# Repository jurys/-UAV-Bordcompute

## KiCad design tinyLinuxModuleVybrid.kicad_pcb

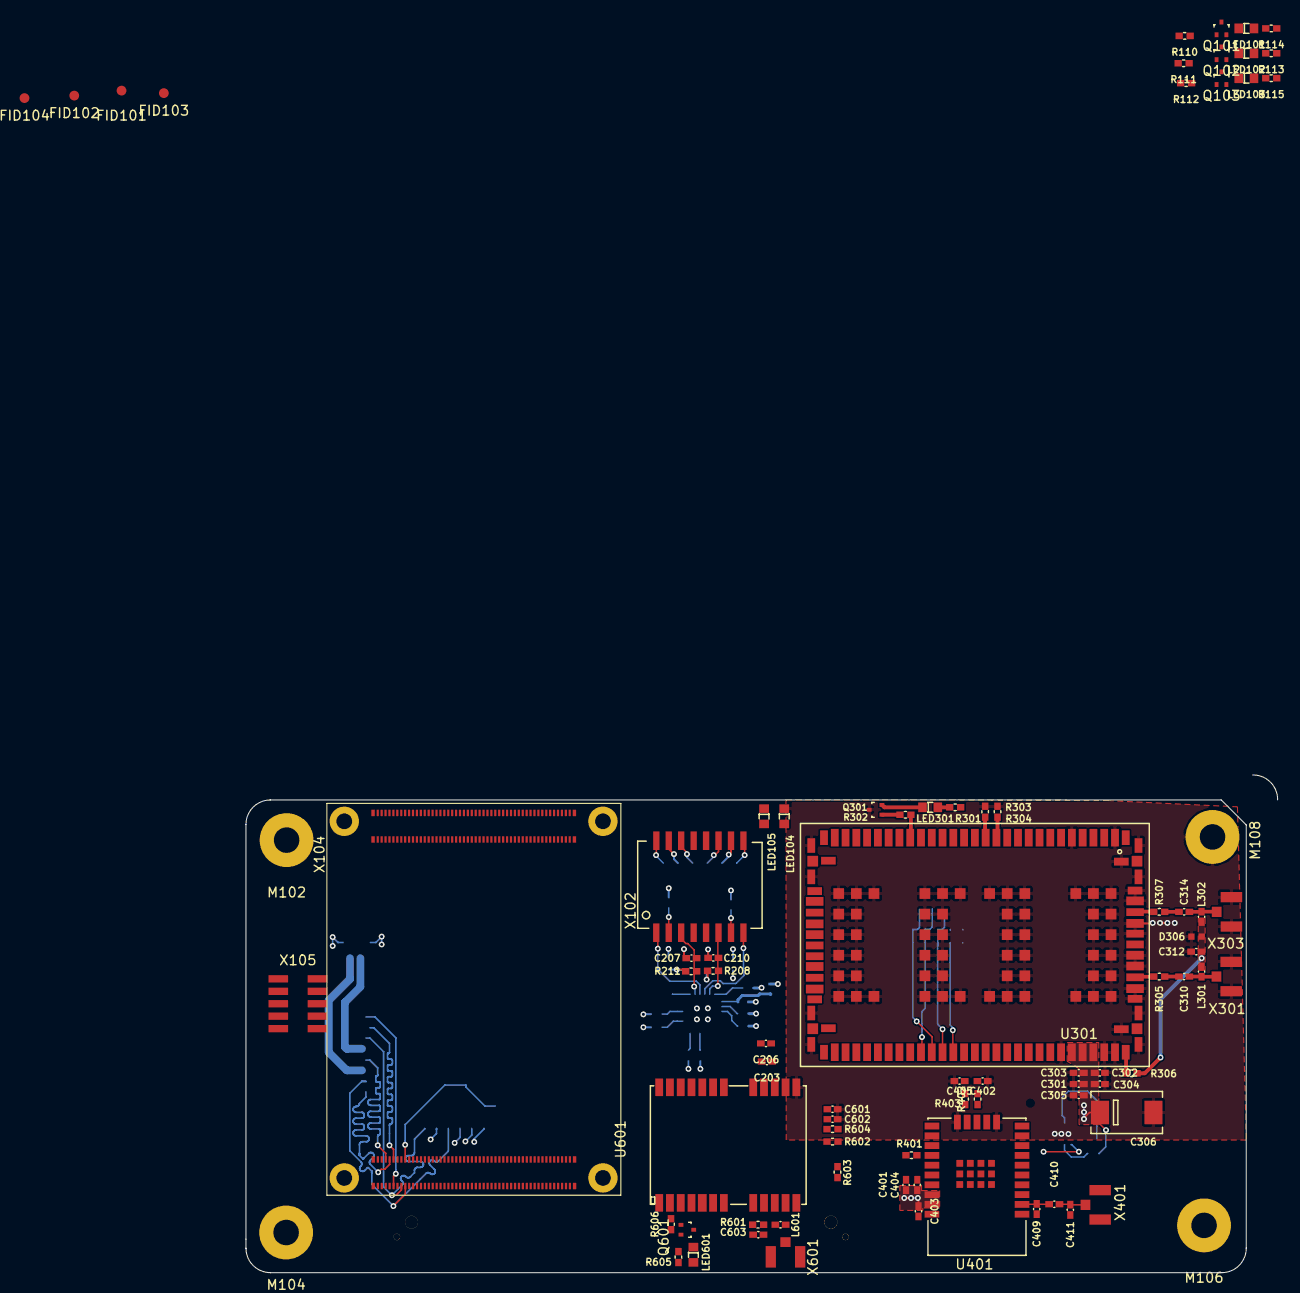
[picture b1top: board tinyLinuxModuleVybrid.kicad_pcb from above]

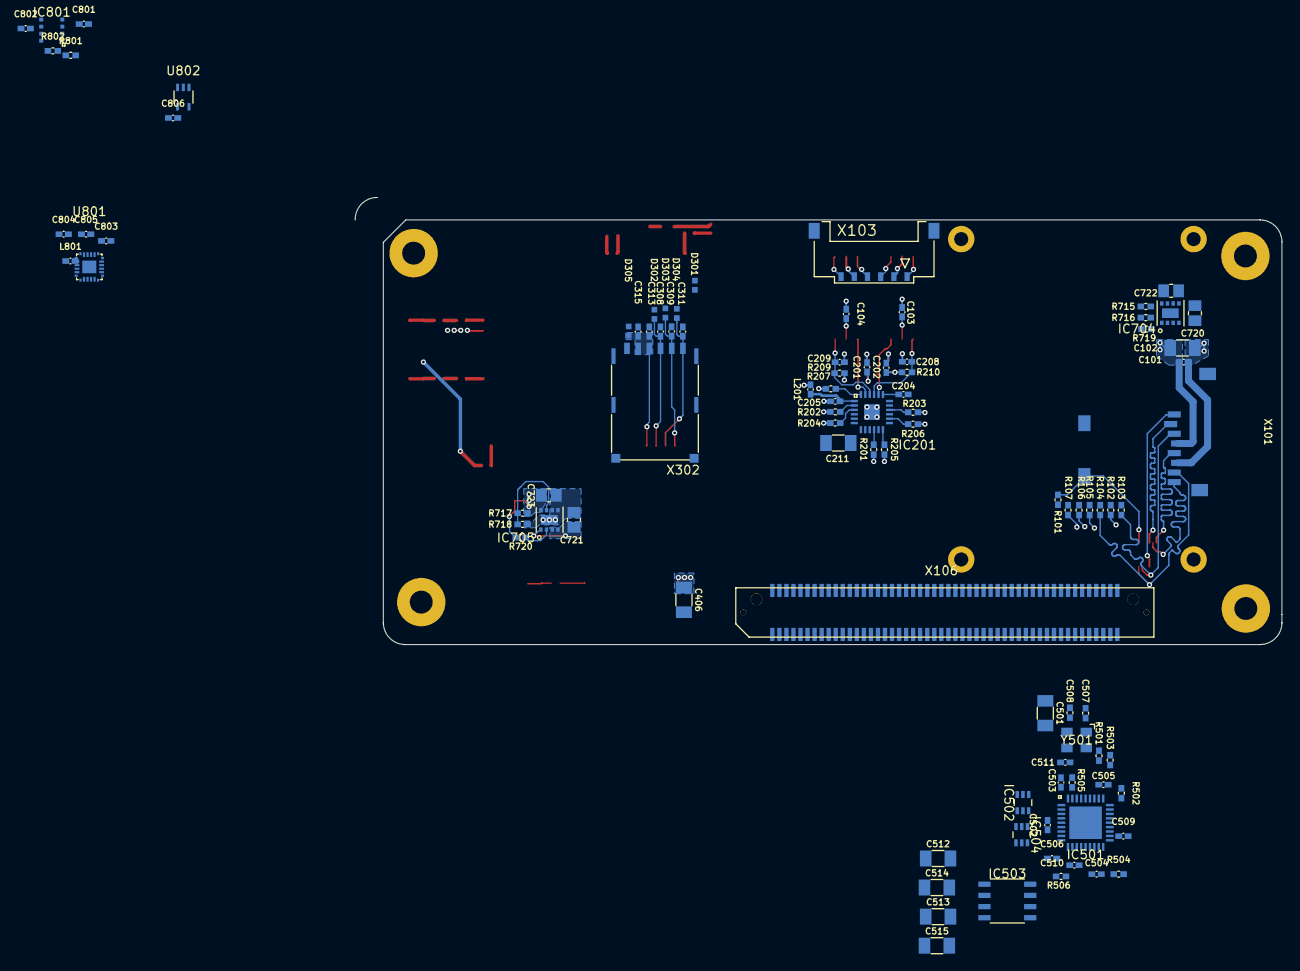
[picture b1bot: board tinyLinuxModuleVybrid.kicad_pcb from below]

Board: 6 copper layers, 105.3 x 50.8 mm, 176 parts (94 on the bottom side), 121 nets.

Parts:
C101, C404, C502, C503, C504, C505, C506, C509, C510, C511, C601, C602, C801, C802, C803, C804, C805, C806: 100n; C0402N
C102, C211, C501, C512, C513, C514, C515: 22u,10V; C1206N
C103, C104, C201, C202, C203, C204, C205, C206: 1u,10V,X5R; C0402N
C207, C208, C209, C210, C401, C402, C403, C405, C410: 10p; C0402N
C301: 68p, 50V; C0402N
C302: 15p, 50V; C0402N
C303: 8.2p, 50V; C0402N
C304: 10n, 50V; C0402N
C305, C315: 100n, 16V; C0402N
C306: 330u, 16V; T520D
C308, C309, C311, C313: 47p, 50V; C0402N
C310, C314: 33p, 50V; C0402N
C312: 27p, 50V; C0402N
C406: 2.2u; C1206N
C409, C411: C; C0402N
C507, C508: 18p; R0402N
C603: 10n, 16V; C0402N
C720, C721: 10u, 10V; C0805N
C722, C723: 22u, 3mOhm; C0805N
D301, D302, D303, D304, D305, D306: DP; D_0402
FID101, FID102, FID103, FID104: FIDUCIAL; FIDUCIAL_1mm
IC201: LAN8720; LAN8720_QFN33
IC501: USB2514B; USB251xB_QFN36
IC502, IC504: WE-TVS-82400274; WE-TVS-82400274_SC70
IC503: TPS2033; TPS203xD
IC704, IC705: TPS82085
IC801: BME680
L201: 600R@100M; B0402N
L301, L302: 68n; L0402N
L601: 27n; L0402N
L801: B; B0402N
LED101, LED104, LED601: G; LED0603N
LED102, LED105: Y; LED0603N
LED103: B; LED0603N
LED301: GREEN; LED0603N
M102, M104, M106, M108: SCREW; SCREW_M2.5
Q101, Q102, Q103, Q301, Q601: 2N7002BKT; SOT416_GSD
R101, R102, R103, R104, R105, R106, R107, R201, R203, R206, R506, R603: 10k; R0402N
R110, R111, R112, R113, R114, R115, R205, R301, R302, R605: 1k; R0402N
R202, R204: 470; R0402N
R207, R505: 12k; R0402N
R208, R209, R210, R211: 49.9R; R0402N
R303, R304, R305, R306, R307, R402, R403, R602, R604: 0; R0402N
R401: 33k; R0402N
R501, R502, R503, R504: 100k; R0402N
R601: 10 Ω ± 10%, min 0.250 W; R0402N
R606: 10; R0402N
R715: 510k; R0402N
R716, R718: 162k; R0402N
R717: 649k; R0402N
R719, R720: 499k; R0402N
R801, R802: 4,7k; R0402N
U301: U-BLOX-TOBY-L2; UBLOX_TOBY_L210
U401: U-BLOX_LILY-W1; UBLOX-LILY-W1
U601: U-BLOX-NEO-M8N; UBLOX_NEO-M8P
U801: MPU-9250
U802: LMT86; R-PDSO-G5
X101: MICROSD; MICROSD_STD
X102: LAN_Transformer; UL94-V0
X103: CONN_01x06; PicoLock_6
X104: VybridBoard
X105: ARM_JTAG_10; PinBox-1.27-02x05-SMT
X106: CONN_02x50; ERF8-50-05.0-L-DV-K-TR
X301, X303, X401, X601: ANT; U.FL-R-SMT
X302: SIMcard; NANO_SIM_693043020611
Y501: 24M,18p; Crystal_3.2x2.5

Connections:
+3V3: C101.1, C102.1, C201.1, C202.1, C206.2, C211.1, C401.2, C403.2, C404.2, C406.2, C501.1, C502.1, C503.1, C504.1, C505.1, C506.1, C509.1, C601.1, C602.1, C722.1, C801.1, C802.1, C805.1, C806.1, IC201.9, IC501.5, IC501.10, IC501.15, IC501.23, IC501.27, IC501.29, IC501.36, IC704.8, IC801.2, IC801.6, IC801.8, L201.1, L801.1, R101.1, R102.1, R103.1, R104.1, R105.1, R106.1, R107.2, R113.2, R114.2, R115.2, R201.1, R205.1, R206.1, R208.1, R209.1, R210.1, R211.1, R301.2, R401.2, R506.1, R605.1, R715.1, R719.1, R801.1, R802.1, U401.8, U401.9, U601.22, U601.23, U801.8, U802.4, U802.5, X101.4, X104.23, X104.25, X104.27, X104.29, X104.31, X104.33, X104.35, X104.37, X105.1
+3V8: C301.1, C302.1, C303.1, C304.1, C305.1, C306.+, C723.1, IC705.8, R717.1, R720.1, U301.70, U301.71, U301.72
+5V: C512.1, C513.1, C720.1, C721.1, IC503.2, IC704.1, IC704.3, IC704.4, IC705.1, IC705.3, IC705.4, X104.196, X104.198, X104.200
/ADC0SE9: U802.3, X104.94
/Communication/ETH_LED_ACT+: LED105.A, R204.2
/Communication/ETH_LED_SPD-: LED104.A, R202.2
/Communication/ETH_RX+: C210.2, IC201.23, R208.2, X102.6
/Communication/ETH_RX-: C209.2, IC201.22, R209.2, X102.8
/Communication/ETH_TX+: C208.2, IC201.21, R210.2, X102.1
/Communication/ETH_TX-: C207.2, IC201.20, R211.2, X102.3
/Communication/LILY/RF: C409.1, C410.2, U401.12
/Communication/LILY/USB+: R403.2, U401.24
/Communication/LILY/USB-: R402.2, U401.23
/Communication/USB_HUB/USBA_D+: IC501.2, IC502.3, U301.28
/Communication/USB_HUB/USBA_D-: IC501.1, IC502.1, U301.27
/Communication/USB_HUB/USBB_D+: C402.2, IC501.4, IC502.4, R402.1
/Communication/USB_HUB/USBB_D-: C405.2, IC501.3, IC502.6, R403.1
/Communication/USB_HUB/USBC_D+: IC501.7, IC504.4
/Communication/USB_HUB/USBC_D-: IC501.6, IC504.6
/Communication/USB_HUB/USBD_D+: IC501.9, IC504.3
/Communication/USB_HUB/USBD_D-: IC501.8, IC504.1
/PTA6: IC201.5, X104.17
/PTA16: IC503.4, X104.76
/PTA17: IC501.13, IC501.17, IC501.19, IC501.21, IC503.5, R506.2, X104.74
/PTC0: R102.2, X101.5, X104.6
/PTC1: R103.2, X101.3, X104.13
/PTC2: R104.2, X101.7, X104.15
/PTC3: R105.2, X101.8, X104.8
/PTC4: R106.2, X101.1, X104.9
/PTC5: R107.1, X101.2, X104.10
/PTC6: R101.2, X101.CD1, X104.16
/PTC9: IC201.13, X104.63
/PTC10: IC201.12, R205.2, X104.65
/PTC11: IC201.11, X104.58
/PTC12: IC201.7, X104.56
/PTC13: IC201.8, X104.20
/PTC14: IC201.10, R201.2, X104.26
/PTC15: IC201.18, X104.24
/PTC16: IC201.17, X104.19
/PTC17: IC201.16, R203.1, X104.43
/PTD21: R110.2, X104.136
/PTD22: R111.2, X104.134
/PTD23: R112.2, X104.138
/Sensors/SCK: IC801.4, R802.2
/Sensors/SDI: IC801.3, R801.2
/TCK: X104.4, X105.4
/TDI: X104.5, X105.8
/TDO: X104.3, X105.6
/TMS: X104.7, X105.2
/USB0_D_N: IC501.30, X104.87
/USB0_D_P: IC501.31, X104.89
/USB0_VBUS: C514.1, C515.1, IC502.5, IC503.6, IC503.7, IC503.8, IC504.5, X104.75
/~RESET: D301.A, IC201.15, IC501.26, U301.23, U601.8, X104.190, X105.10
GND: C101.2, C102.2, C103.2, C104.2, C201.2, C202.2, C203.1, C204.1, C205.1, C206.1, C207.1, C208.1, C209.1, C210.1, C211.2, C301.2, C302.2, C303.2, C304.2, C305.2, C306.-, C308.2, C309.2, C311.2, C312.1, C313.2, C315.2, C401.1, C402.1, C403.1, C404.1, C405.1, C406.1, C409.2, C411.2, C501.2, C502.2, C503.2, C504.2, C505.2, C506.2, C507.2, C508.2, C509.2, C510.2, C511.2, C512.2, C513.2, C514.2, C515.2, C601.2, C602.2, C603.2, C720.2, C721.2, C722.2, C723.2, C801.2, C802.2, C803.2, C804.2, C805.2, C806.2, D301.C, D302.A, D303.A, D304.A, D305.A, D306.C, IC201.P, IC501.11, IC501.P, IC502.2, IC503.1, IC504.2, IC704.5, IC704.6, IC704.P, IC705.5, IC705.6, IC705.P, IC801.1, IC801.7, LED104.C, LED105.C, M102.1, M104.1, M106.1, M108.1, Q101.S, Q102.S, Q103.S, Q301.D, Q601.S, R203.2, R207.2, R303.2, R304.2, R501.2, R502.2, R503.2, R504.2, R505.2, R603.2, R716.2, R718.2, U301.2, U301.6, U301.30, U301.32, U301.44, U301.46, U301.69, U301.73, U301.74, U301.76, U301.78, U301.79, U301.80, U301.82, U301.83, U301.85, U301.86, U301.88, U301.89, U301.90, U301.92, U301.93, U301.94, U301.95, U301.96, U301.97, U301.98, U301.99, U301.100, U301.101, U301.102, U301.103, U301.104, U301.105, U301.106, U301.107, U301.108, U301.109, U301.110, U301.111, U301.112, U301.113, U301.114, U301.115, U301.116, U301.117, U301.118, U301.119, U301.120, U301.121, U301.122, U301.123, U301.124, U301.125, U301.126, U301.127, U301.128, U301.129, U301.130, U301.131, U301.132, U301.133, U301.134, U301.135, U301.136, U301.137, U301.138, U301.139, U301.140, U301.141, U301.142, U301.143, U301.144, U301.145, U301.146, U301.147, U301.148, U301.149, U301.150, U401.6, U401.10, U401.11, U401.13, U401.21, U401.25, U401.26, U401.27, U401.28, U401.29, U401.30, U401.31, U401.32, U401.33, U401.34, U401.35, U401.36, U401.37, U601.7, U601.10, U601.12, U601.13, U601.24, U801.11, U801.18, U801.20, U802.1, U802.2, X101.6, X101.CD2, X101.MT, X102.10, X102.15, X103.2, X103.5, X104.1, X104.2, X104.11, X104.12, X104.21, X104.22, X104.32, X104.41, X104.42, X104.47, X104.52, X104.57, X104.62, X104.67, X104.69, X104.71, X104.72, X104.73, X104.79, X104.82, X104.85, X104.91, X104.92, X104.111, X104.112, X104.121, X104.122, X104.131, X104.132, X104.141, X104.142, X104.151, X104.152, X104.161, X104.162, X104.171, X104.172, X104.181, X104.182, X104.191, X104.192, X104.194, X104.M1, X104.M2, X104.M3, X104.M4, X104.M5, X104.M6, X104.M7, X104.M8, X105.3, X105.5, X301.P, X302.C5, X302.P, X303.P, X401.P, X601.P, Y501.S1, Y501.S2
unnamed: C103.1, X102.2
unnamed: C104.1, X102.7
unnamed: C203.2, IC201.6
unnamed: C204.2, C205.2, IC201.1, IC201.19, L201.2
unnamed: C308.1, D302.C, U301.58, X302.C2
unnamed: C309.1, D303.C, U301.56, X302.C3
unnamed: C310.1, L301.2, X301.1
unnamed: C310.2, R305.1
unnamed: C311.1, D304.C, U301.57, X302.C7
unnamed: C312.2, D306.A, L301.1, L302.1, R306.1
unnamed: C313.1, C315.1, D305.C, U301.59, X302.C1, X302.C6
unnamed: C314.1, L302.2, X303.1
unnamed: C314.2, R307.1
unnamed: C410.1, C411.1, X401.1
unnamed: C507.1, IC501.33, Y501.1
unnamed: C508.1, IC501.32, Y501.2
unnamed: C510.1, IC501.14
unnamed: C511.1, IC501.34
unnamed: C603.1, L601.2, R601.1
unnamed: C803.1, U801.10
unnamed: C804.1, L801.2, U801.13
unnamed: IC201.2, R202.1
unnamed: IC201.3, R204.1
unnamed: IC201.14, R206.2
unnamed: IC201.24, R207.1
unnamed: IC501.22, R504.1
unnamed: IC501.24, R503.1
unnamed: IC501.25, R502.1
unnamed: IC501.28, R501.1
unnamed: IC501.35, R505.1
unnamed: IC704.2, R719.2
unnamed: IC704.7, R715.2, R716.1
unnamed: IC705.2, R720.2
unnamed: IC705.7, R717.2, R718.1
unnamed: L601.1, U601.11, X601.1
unnamed: LED101.A, R113.1
unnamed: LED101.C, Q101.D
unnamed: LED102.A, R114.1
unnamed: LED102.C, Q102.D
unnamed: LED103.A, R115.1
unnamed: LED103.C, Q103.D
unnamed: LED301.A, R301.1
unnamed: LED301.C, Q301.S
unnamed: LED601.A, R605.2
unnamed: LED601.C, Q601.D
unnamed: Q101.G, R110.1
unnamed: Q102.G, R111.1
unnamed: Q103.G, R112.1
unnamed: Q301.G, R302.2
unnamed: Q601.G, R606.2
unnamed: R302.1, U301.21
unnamed: R303.1, U301.14
unnamed: R304.1, U301.13
unnamed: R305.2, U301.81
unnamed: R306.2, U301.75
unnamed: R307.2, U301.87
unnamed: R401.1, U401.4
unnamed: R601.2, U601.9
unnamed: R602.1, U601.20
unnamed: R603.1, U601.14
unnamed: R604.1, U601.21
unnamed: R606.1, U601.3
unnamed: U301.1, U301.7, U301.8, U301.9, U301.18, U301.19, U301.29, U301.31, U301.33, U301.34, U301.35, U301.36, U301.37, U301.38, U301.39, U301.40, U301.41, U301.42, U301.43, U301.45, U301.47, U301.48, U301.49, U301.77, U301.84, U301.91
unnamed: X102.9, X103.6
unnamed: X102.11, X103.4
unnamed: X102.14, X103.3
unnamed: X102.16, X103.1

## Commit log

2016-04-16 Version_1
2016-04-17 libs hizugefügt
2016-04-17 gitignore erstellt
2016-04-18 LILY notitzen hinzugefügt
2016-04-18 USB sheat erstellt
2016-04-19 added footprintadded footprintss
2016-04-21 NEO_modifiziert
2016-04-21 NEO_entfernt
2016-04-21 .gitignore__modifiziert
2016-04-23 3V8 footprints ergänzt
2016-04-24 SimCard footprint ergänzt
2016-04-25 LAN Transformer footprint ergänzt
2016-04-27 NEO N8P durch M8N ersätzt
2016-04-28 LILY Antenne hinzugefügt
2016-04-29 footprints ergänzt
2016-05-01 added some footprints
2016-05-02 added footprints
2016-05-04 adjusted power supply
2016-05-06 adjusted power supply and sensors
2016-05-06 adjusted 3d models
2016-05-08 sorted components
2016-05-14 selected connector pins
2016-05-20 Toby Antenne und Simkarte gerootet
2016-05-25 power Sypply for Tobyfinish
2016-08-14 stecker hinzugefügt
2016-08-16 sd card
